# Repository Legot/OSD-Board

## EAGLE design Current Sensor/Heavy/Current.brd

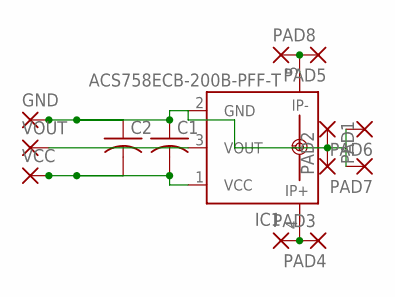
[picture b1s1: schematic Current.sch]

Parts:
C1, C2: C-USC0805K; C0805K
GND: SMD2; SMD1,27-2,54
IC1: ACS758ECB-200B-PFF-T; CB-PFF
PAD1, PAD2, PAD3, PAD4, PAD5, PAD6, PAD7, PAD8: SMD5; SMD2,54-5,08
VCC: SMD2; SMD1,27-2,54
VOUT: SMD2; SMD1,27-2,54

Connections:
5: C1.1, C2.1, GND.1, IC1.2 (GND), PAD1.1, PAD2.1, PAD6.1, PAD7.1
unnamed: IC1.4 (IP+), PAD3.1, PAD4.1
unnamed: IC1.5 (IP-), PAD5.1, PAD8.1
unnamed: C1.2, C2.2, IC1.1 (VCC), VCC.1
unnamed: IC1.3 (VOUT), VOUT.1

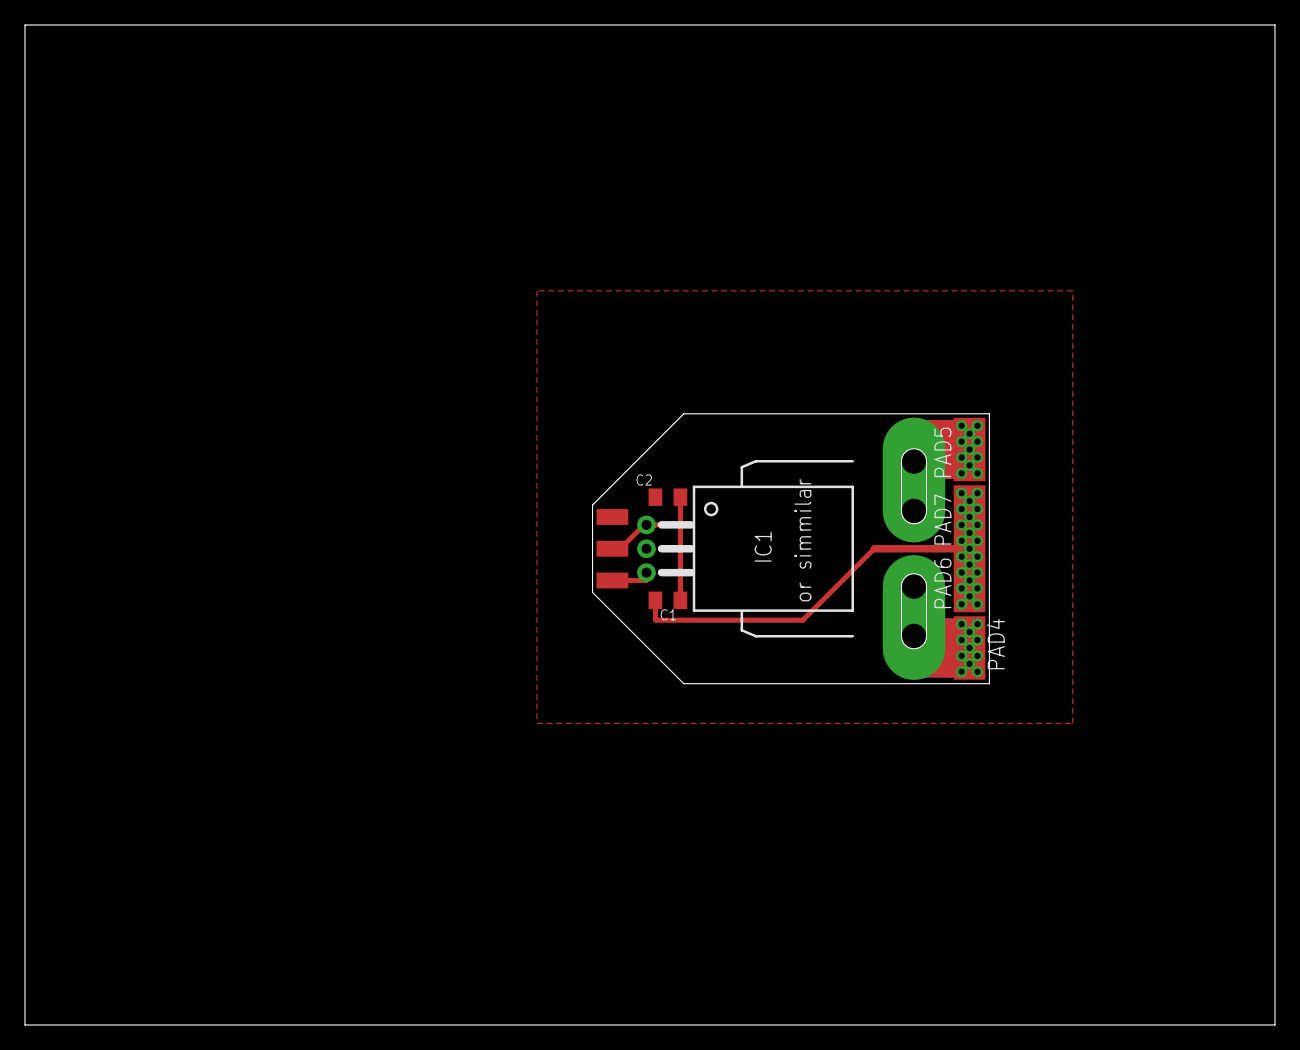
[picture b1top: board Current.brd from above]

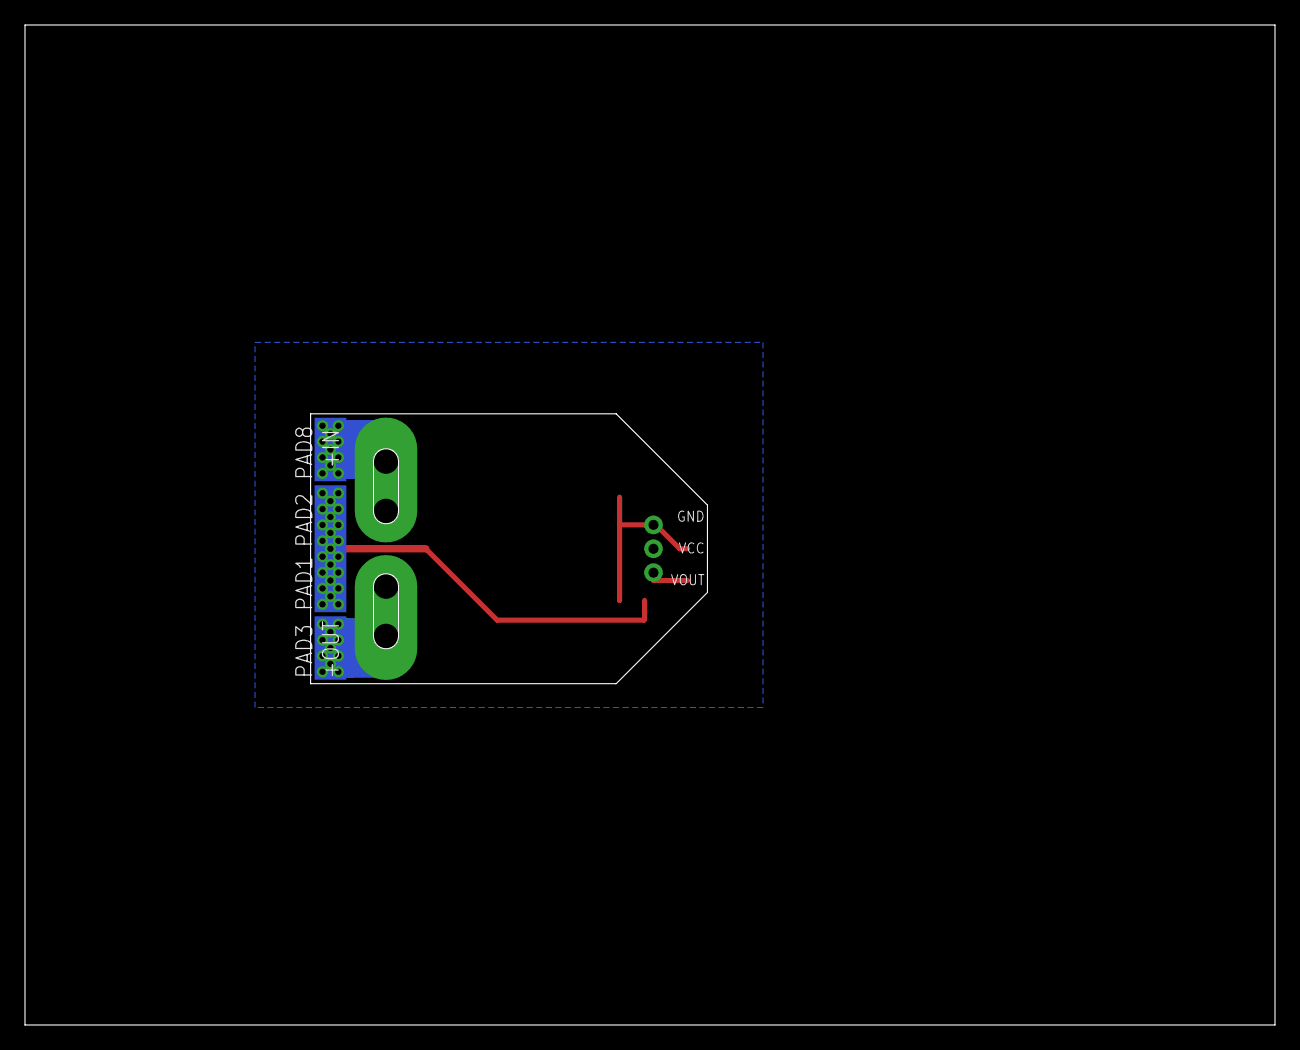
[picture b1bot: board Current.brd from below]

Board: 2 copper layers, 100.0 x 80.0 mm, 14 parts (4 on the bottom side), 5 nets.
